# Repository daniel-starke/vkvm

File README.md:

vkvm
====

**V**irtual **K**eyboard **V**ideo **M**ouse equipment.  
This project consists of a software part which runs on the host (controller) computer and a hardware
unit (periphery). The periphery is connected via HDMI and USB to the USB port at the controller. The
controller uses this connection to control the connected periphery computer. Control works similar to
the control of a system running within a virtual machine.  
The vkvm ensures a non-intrusive connection to the periphery device. Therefore, no special drivers or
software is needed at the periphery. This grants maximum compatibility and high security not found in
VPN or SSH like solutions and works also before OS start-up (e.g. remote BIOS control).

```txt
+------------+       +----------------------+      +---------------+
|            |  <--- | Video Capture Device | <--- |               |
| Controller |       +----------------------+      | Remote Device |
|            |  <--> | VKVM Periphery       | <--> |               |
+------------+       +----------------------+      +---------------+
```

Features
========

- control application support for Windows and Linux
- USB UVC capture device compatible at controller
- USB HID boot keyboard/mouse compatible at periphery
- easy setup and use via plug'n'play
- cheap, small, low latency and portable design
- supports direct video output capture of periphery or web cam based operation
- multiple hardware variants are available to meet different hardware assembly skills and usage requirements
- remote device access before OS startup (e.g. enter BitLocker password or set BIOS settings)

Usage
=====

Use an available display to USB (not the other way around) converter to capture the video output
of a periphery machine at the controller. See chapter example for some possible variants. Connect
the VKVM hardware device to controller and periphery to control the keyboard and mouse of the
periphery via the controller. The vkvm control application enables you to perform the described hardware
connection on software level.  
Here you choose the connected capture source and serial interface which connects the vkvm hardware.
Click into the video frame to start controlling the remote device. Hit the right SHIFT and right CTRL key
to return control. Alternatively, press CTRL-K without a connected capture source for blind control.
This can be useful when controlling the periphery device with a connected physical monitor.  
To improve periphery operation, multiple ways of inputting data from controller (paste text) are provided.
Each type exists due to different compatibilities, either by applications or on OS level.  
Most of the user interface is made up of icons to avoid language barriers.

Status LED of the VKVM periphery:

|LED                  |State     |Meaning
|:-------------------:|----------|------------------------------------------------
|                     |always off|No remote device connected.
||blinking  |Power from remote device but not USB connection.
||always on |Fully connected to remote device.

Documentation
=============

- [Windows: VKVM Control Driver Installation](doc/win-driver.md)
- [Hardware](doc/hardware.md)
- [Software Architecture](doc/architecture.md)
- [Serial Protocol](doc/protocol.md)

Building
========

The following dependencies are given.  
Controller:  
- C99
- C++11
- [FLTK 1.3.4-1](https://github.com/fltk/fltk/tree/release-1.3.4-1)
- [nanosvg](https://github.com/memononen/nanosvg) (modified source included)
- OpenGL
- DirectShow (only on Windows)
- libv4l2 (only on Linux)
- lv4lconvert (only on Linux)

Periphery:  
- C18
- C++14
- [PlatformIO](https://platformio.org/)
- [STM32CubeDuino](https://github.com/daniel-starke/STM32CubeDuino)
- [HidDescCTC](https://github.com/daniel-starke/HidDescCTC)

Choose the appropriate Makefile to match your target system configuration.  
Windows with MinGW and GCC:  
```sh
make -f Makefile.mingw
```

Linux with GCC:
```sh
make -f Makefile.linux
```

This creates two applications:
- `vkvm`  
  The actual VKVM control application.
- `keyTest`  
  Development tool to create the OS key code to USB key code mapping.

To build and upload the firmware (depending on the target hardware):
```sh
pio run -e arduino -t upload
pio run -e vkm-b-controller -t upload
pio run -e vkm-b-periphery -t upload
```

Note that `VKVM_LED_PWM` for `vkm-b-periphery` can be changed in `platformio.ini` to any value
between 0 and 65535 to adjust the brightness of the status LED.

Also note that it is possible to set `upload_protocol = dfu` for `STM32CubeDuino` in `platformio.ini`
allowing first time programming via USB.

Open Points
===========

- [ ] command-line operations for instant video/serial connect and full screen switch
- [ ] automatically reconnect last serial/video device if it re-appears and was not disconnected by user
- [ ] alternative serial/video implementation using libusb/libuvc
- [ ] force aspect ratio option in aspect ratio button
- [ ] audio support
- [ ] configurable hot keys
- [ ] media key support (needs changes in the periphery firmware)
- [ ] fast store and load option for capture source settings
- [ ] option for file exchange via USB MTP (media transfer protocol)
- [ ] option for shared network access via USB ECM (Ethernet control model)

Limitation
==========

- keyboard and mouse input may not work with the Arduino firmware variant due to legacy BIOS
  incompatibilities with the CDC interface included by Arduino
- no OCR support (out of scope and can be done with existing screen reader applications)
- root permissions are required for the vkvm application on Linux

Debugging
=========

Choose the appropriate Makefile to match your target system configuration.  
Windows with MinGW and GCC:  
```sh
make -f Makefile.mingw DEBUG=1
```

Linux with GCC:
```sh
make -f Makefile.linux DEBUG=1
```

The macro `VKVM_TRACE` can be defined to create the serial trace file `vkvm.log`
during runtime. The GAWK script `script/prot-dec.awk` is able to decode this file into
a human readable format. The macro can be enabled by passing `TRACE=1` to Gnumake.

To debug the periphery firmware run:
```sh
pio debug -e vkm-b-periphery
pio run -e vkm-b-periphery -t upload -t nobuild
pio debug  -e vkm-b-periphery --interface=gdb -- -x .pioinit
```

The HID reports on the periphery device can be traced using
Wireshark (see [description](https://wiki.wireshark.org/CaptureSetup/USB)).

In Linux it is also possible to read and analyze the HID reports
with the following command:
```sh
cat /sys/kernel/debug/<dev>/events
```

This shows how the Linux HID driver interprets the HID reports.

License
=======

See [LICENSE](LICENSE).  

Contributions
=============

No content contributions are accepted. Please file a bug report or feature request instead.  
This decision was made in consideration of the used license.

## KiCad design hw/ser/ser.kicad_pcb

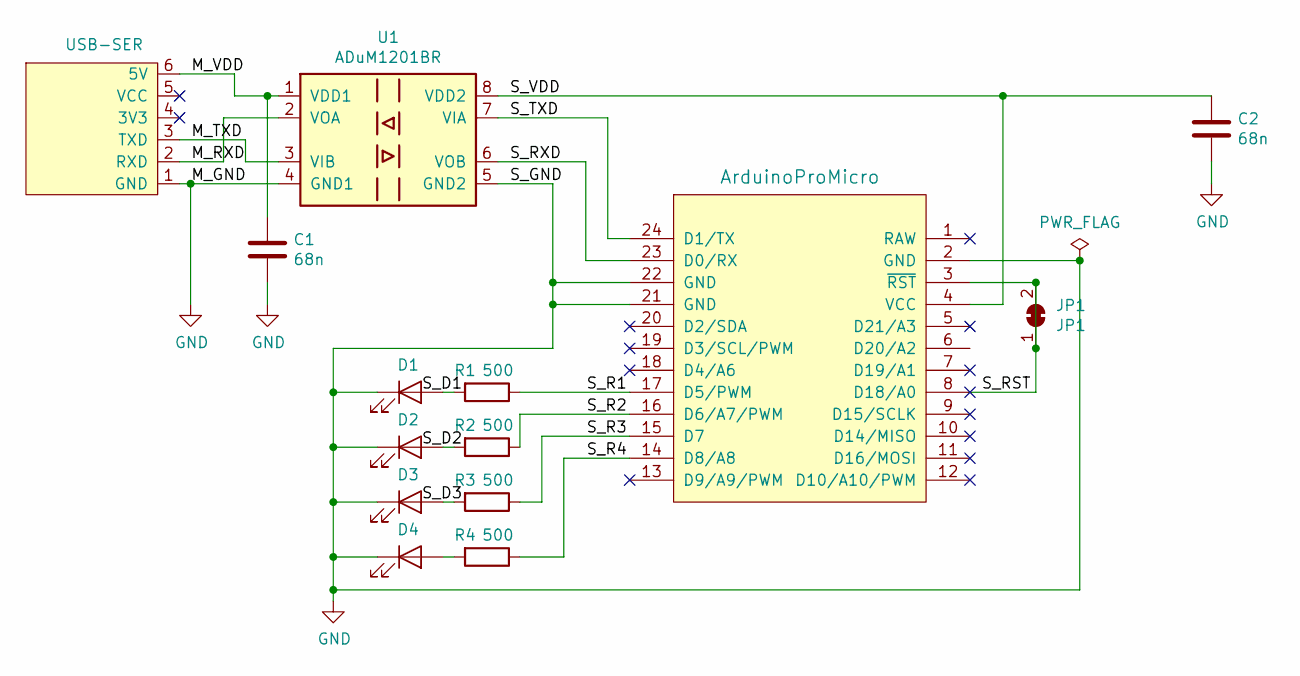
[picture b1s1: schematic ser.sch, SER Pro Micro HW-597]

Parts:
C1, C2: 68n; C_0603_1608Metric_Pad1.05x0.95mm_HandSolder
D1, D2, D3, D4: LED; LED_0603_1608Metric_Pad1.05x0.95mm_HandSolder
IC1: ArduinoProMicro; ArduinoProMicro_Custom
JP1: JP1; SolderJumper-2_P1.3mm_Bridged_Pad1.0x1.5mm
JT1: USB-SER; PinHeader_1x06_P2.54mm_Vertical_Custom
R1, R2, R3, R4: 500; R_0603_1608Metric_Pad1.05x0.95mm_HandSolder
U1: ADuM1201BR; SOIC-8_3.9x4.9mm_P1.27mm

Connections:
/M_RXD: JT1.2 (RXD), U1.2 (VOA)
/M_TXD: JT1.3 (TXD), U1.3 (VIB)
/M_VDD: C1.1, JT1.6 (5V), U1.1 (VDD1)
/S_R1: IC1.17 (D5/PWM), R1.1
/S_R2: IC1.16 (D6/A7/PWM), R2.1
/S_R3: IC1.15 (D7), R3.1
/S_R4: IC1.14 (D8/A8), R4.1
/S_RST: IC1.3 (~RST), IC1.8 (D18/A0), JP1.1 (A), JP1.2 (B)
/S_RXD: IC1.23 (D0/RX), U1.6 (VOB)
/S_TXD: IC1.24 (D1/TX), U1.7 (VIA)
/S_VDD: C2.1, IC1.4 (VCC), U1.8 (VDD2)
GND: C1.2, C2.2, D1.1 (K), D2.1 (K), D3.1 (K), D4.1 (K), IC1.2 (GND), IC1.21 (GND), IC1.22 (GND), JT1.1 (GND), U1.4 (GND1), U1.5 (GND2)
unnamed: D1.2 (A), R1.2
unnamed: D2.2 (A), R2.2
unnamed: D3.2 (A), R3.2
unnamed: D4.2 (A), R4.2

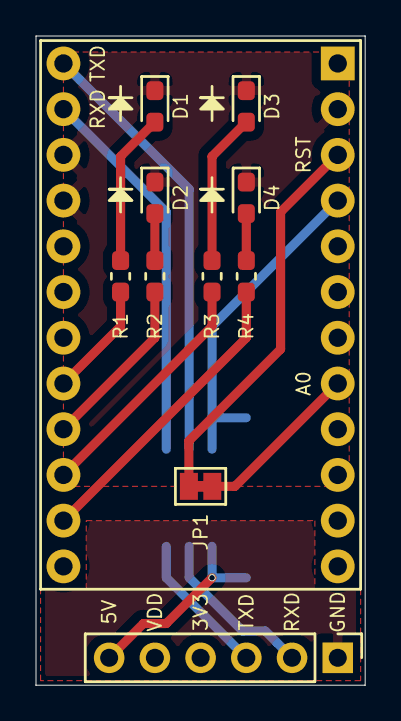
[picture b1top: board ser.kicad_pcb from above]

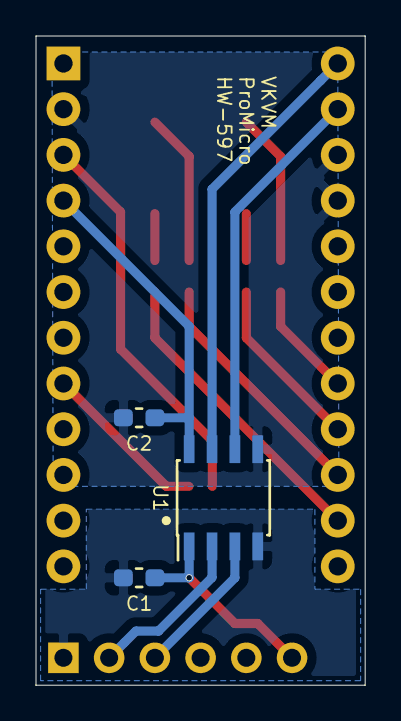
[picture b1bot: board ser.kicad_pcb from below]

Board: 2 copper layers, 18.3 x 36.1 mm, 14 parts (3 on the bottom side), 16 nets.

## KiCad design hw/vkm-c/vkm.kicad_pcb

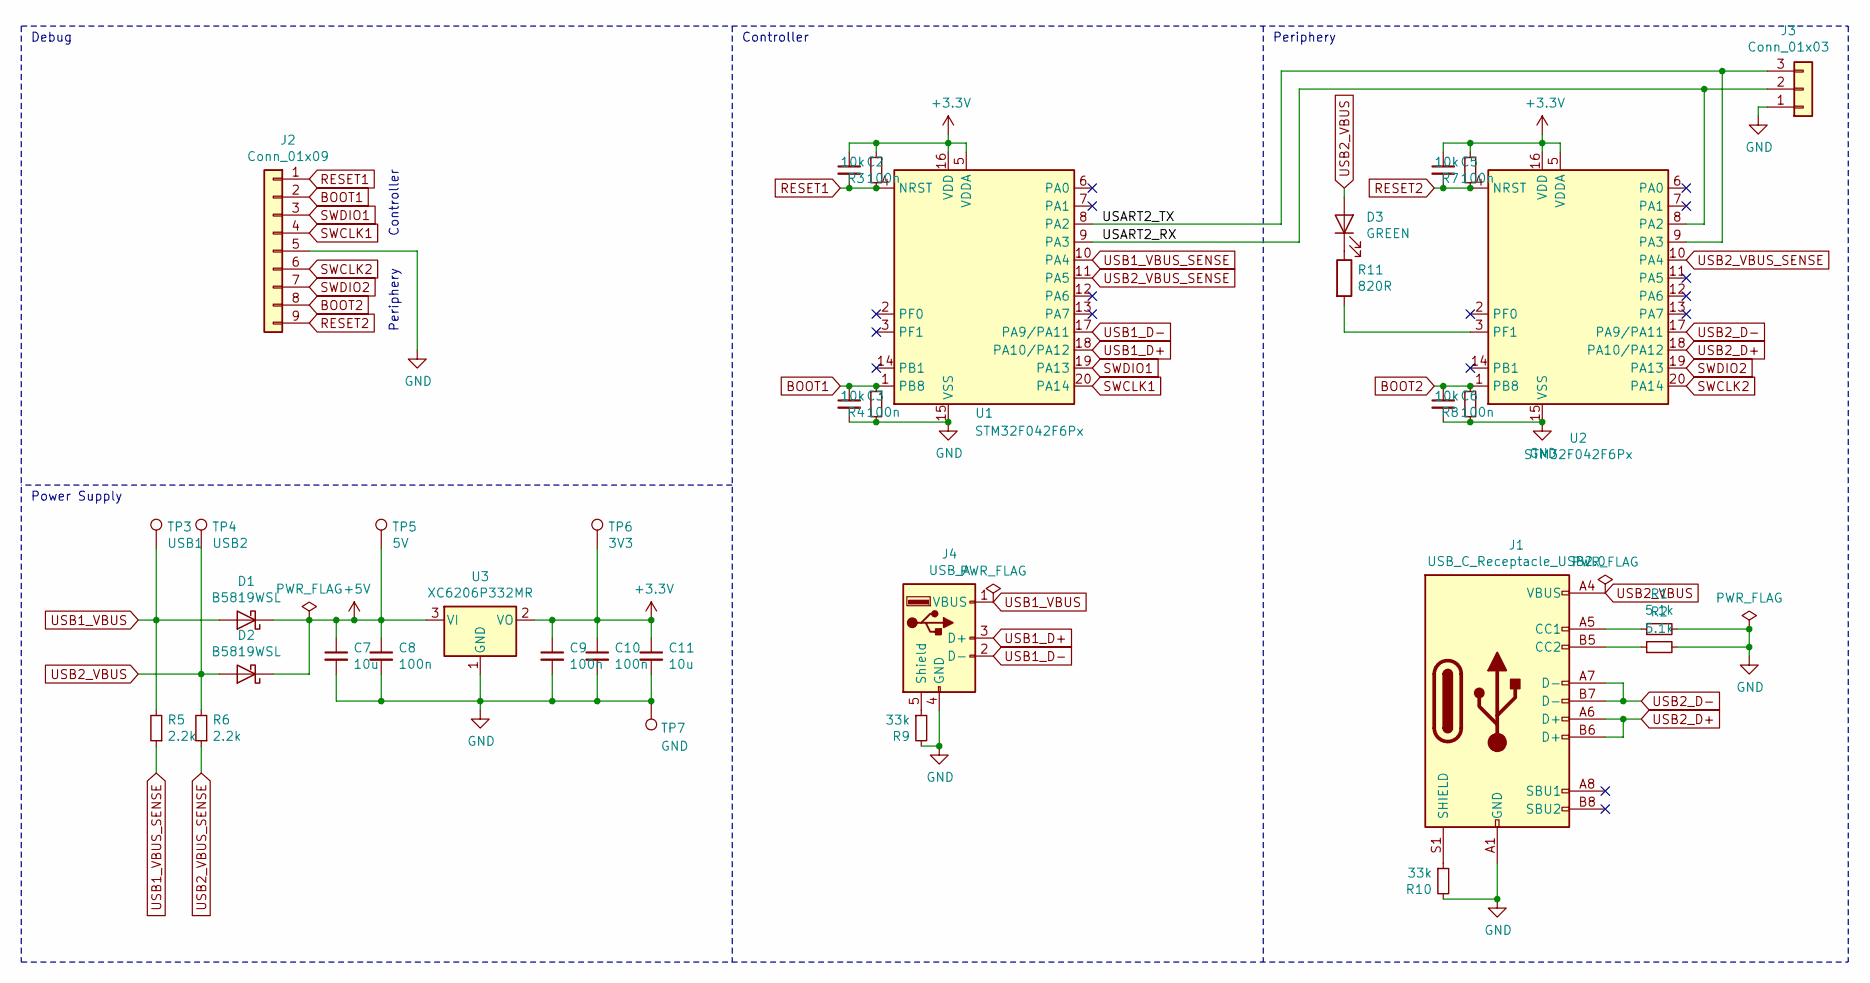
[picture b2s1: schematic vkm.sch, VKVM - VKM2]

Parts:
C2, C3, C5, C6, C8, C9, C10: 100n; C_0603_1608Metric; LCSC C14663
C7, C11: 10u; C_0603_1608Metric; LCSC C19702
D1, D2: B5819WSL; D_SOD-123; LCSC C8598
D3: GREEN; LED_0603_1608Metric; LCSC C72043
J1: USB_C_Receptacle_USB2.0; USB_C_HRO_TYPE_C_31_M_12; LCSC C165948
J2: Conn_01x09; PinHeader_1x09_P2.54mm_Vertical
J3: Conn_01x03; PinHeader_1x03_P2.54mm_Horizontal_Edge
J4: USB_A; USB_A_TH_AM90; LCSC C9739
R1, R2: 5.1k; R_0603_1608Metric; LCSC C23186
R3, R4, R7, R8: 10k; R_0603_1608Metric; LCSC C25804
R5, R6: 2.2k; R_0603_1608Metric; LCSC C4190
R9, R10: 33k; R_0603_1608Metric; LCSC C4216
R11: 820R; R_0603_1608Metric; LCSC C23253
TP3: USB1; TestPoint_Pad_D1.0mm
TP4: USB2; TestPoint_Pad_D1.0mm
TP5: 5V; TestPoint_Pad_D1.0mm
TP6: 3V3; TestPoint_Pad_D1.0mm
TP7: GND; TestPoint_Pad_D1.0mm
U1, U2: STM32F042F6Px; TSSOP-20_4.4x6.5mm_P0.65mm; LCSC C81000
U3: XC6206P332MR; SOT-23; LCSC C5446

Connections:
+3V3: C2.1, C5.1, C9.1, C10.1, C11.1, R3.1, R7.1, TP6.1, U1.5 (VDDA), U1.16 (VDD), U2.5 (VDDA), U2.16 (VDD), U3.2 (VO)
+5V: C7.1, C8.1, D1.1 (K), D2.1 (K), TP5.1, U3.3 (VI)
/USART2_RX: J3.2, U1.9 (PA3), U2.8 (PA2)
/USART2_TX: J3.3, U1.8 (PA2), U2.9 (PA3)
BOOT1: C3.1, J2.2, R4.1, U1.1 (PB8)
BOOT2: C6.1, J2.8, R8.1, U2.1 (PB8)
GND: C3.2, C6.2, C7.2, C8.2, C9.2, C10.2, C11.2, J1.A1 (GND), J1.A12 (GND), J1.B1 (GND), J1.B12 (GND), J2.5, J3.1, J4.4 (GND), R1.2, R2.2, R4.2, R8.2, R9.2, R10.2, TP7.1, U1.15 (VSS), U2.15 (VSS), U3.1 (GND)
unnamed: D3.1 (K), R11.1
unnamed: J1.A5 (CC1), R1.1
unnamed: J1.B5 (CC2), R2.1
unnamed: J1.S1 (SHIELD), R10.1
unnamed: J4.5 (Shield), R9.1
unnamed: R11.2, U2.3 (PF1)
RESET1: C2.2, J2.1, R3.2, U1.4 (NRST)
RESET2: C5.2, J2.9, R7.2, U2.4 (NRST)
SWCLK1: J2.4, U1.20 (PA14)
SWCLK2: J2.6, U2.20 (PA14)
SWDIO1: J2.3, U1.19 (PA13)
SWDIO2: J2.7, U2.19 (PA13)
USB1_D+: J4.3 (D+), U1.18 (PA10/PA12)
USB1_D-: J4.2 (D-), U1.17 (PA9/PA11)
USB1_VBUS: D1.2 (A), J4.1 (VBUS), R5.2, TP3.1
USB1_VBUS_SENSE: R5.1, U1.10 (PA4)
USB2_D+: J1.A6 (D+), J1.B6 (D+), U2.18 (PA10/PA12)
USB2_D-: J1.A7 (D-), J1.B7 (D-), U2.17 (PA9/PA11)
USB2_VBUS: D2.2 (A), D3.2 (A), J1.A4 (VBUS), J1.A9 (VBUS), J1.B4 (VBUS), J1.B9 (VBUS), R6.2, TP4.1
USB2_VBUS_SENSE: R6.1, U1.11 (PA5), U2.10 (PA4)

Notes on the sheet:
Controller
Periphery
Debug
Power Supply

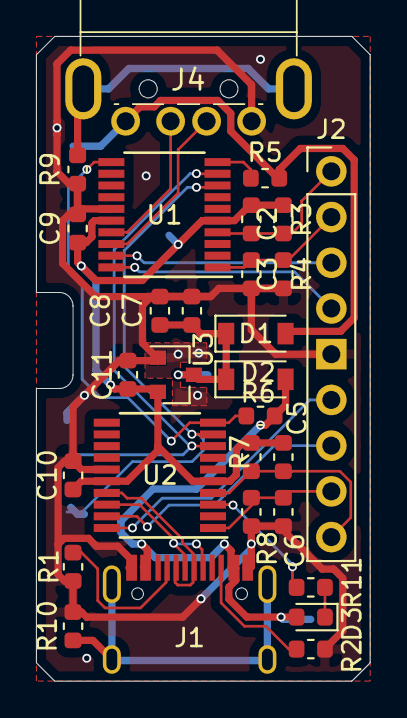
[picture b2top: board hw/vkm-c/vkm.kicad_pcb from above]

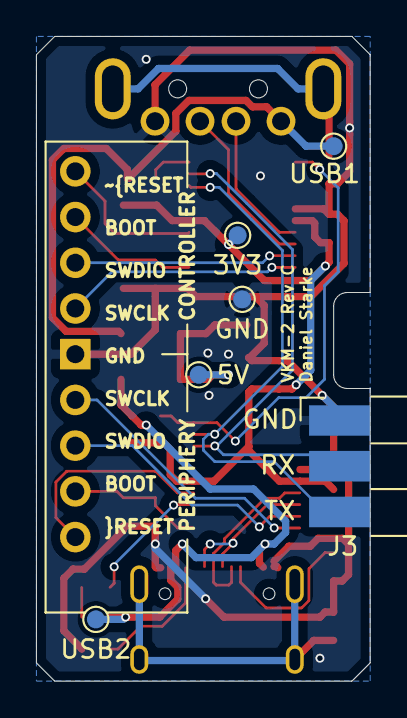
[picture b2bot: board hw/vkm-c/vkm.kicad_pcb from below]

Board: 2 copper layers, 18.5 x 35.8 mm, 35 parts (6 on the bottom side), 27 nets.

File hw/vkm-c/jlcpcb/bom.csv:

Comment,Designator,Footprint,LCSC
10u,"C7,C11",Capacitor_SMD:C_0603_1608Metric,C19702
100n,"C8,C9,C10,C2,C3,C6,C5",Capacitor_SMD:C_0603_1608Metric,C14663
B5819WSL,"D1,D2",Diode_SMD:D_SOD-123,C8598
GREEN,D3,LED_SMD:LED_0603_1608Metric,C72043
USB_C_Receptacle_USB2.0,J1,Connector_USB:USB_C_HRO_TYPE_C_31_M_12,C165948
Conn_01x09,J2,Connector_PinHeader_2.54mm:PinHeader_1x09_P2.54mm_Vertical,
Conn_01x03,J3,vkm-c:PinHeader_1x03_P2.54mm_Horizontal_Edge,
USB_A,J4,Connector_USB:USB_A_TH_AM90,C9739
5.1k,"R1,R2",Resistor_SMD:R_0603_1608Metric,C23186
33k,"R10,R9",Resistor_SMD:R_0603_1608Metric,C4216
820R,R11,Resistor_SMD:R_0603_1608Metric,C23253
10k,"R3,R7,R4,R8",Resistor_SMD:R_0603_1608Metric,C25804
2.2k,"R6,R5",Resistor_SMD:R_0603_1608Metric,C4190
USB1,TP3,TestPoint:TestPoint_Pad_D1.0mm,
USB2,TP4,TestPoint:TestPoint_Pad_D1.0mm,
5V,TP5,TestPoint:TestPoint_Pad_D1.0mm,
3V3,TP6,TestPoint:TestPoint_Pad_D1.0mm,
GND,TP7,TestPoint:TestPoint_Pad_D1.0mm,
STM32F042F6Px,"U1,U2",Package_SO:TSSOP-20_4.4x6.5mm_P0.65mm,C81000
XC6206P332MR,U3,Package_TO_SOT_SMD:SOT-23,C5446

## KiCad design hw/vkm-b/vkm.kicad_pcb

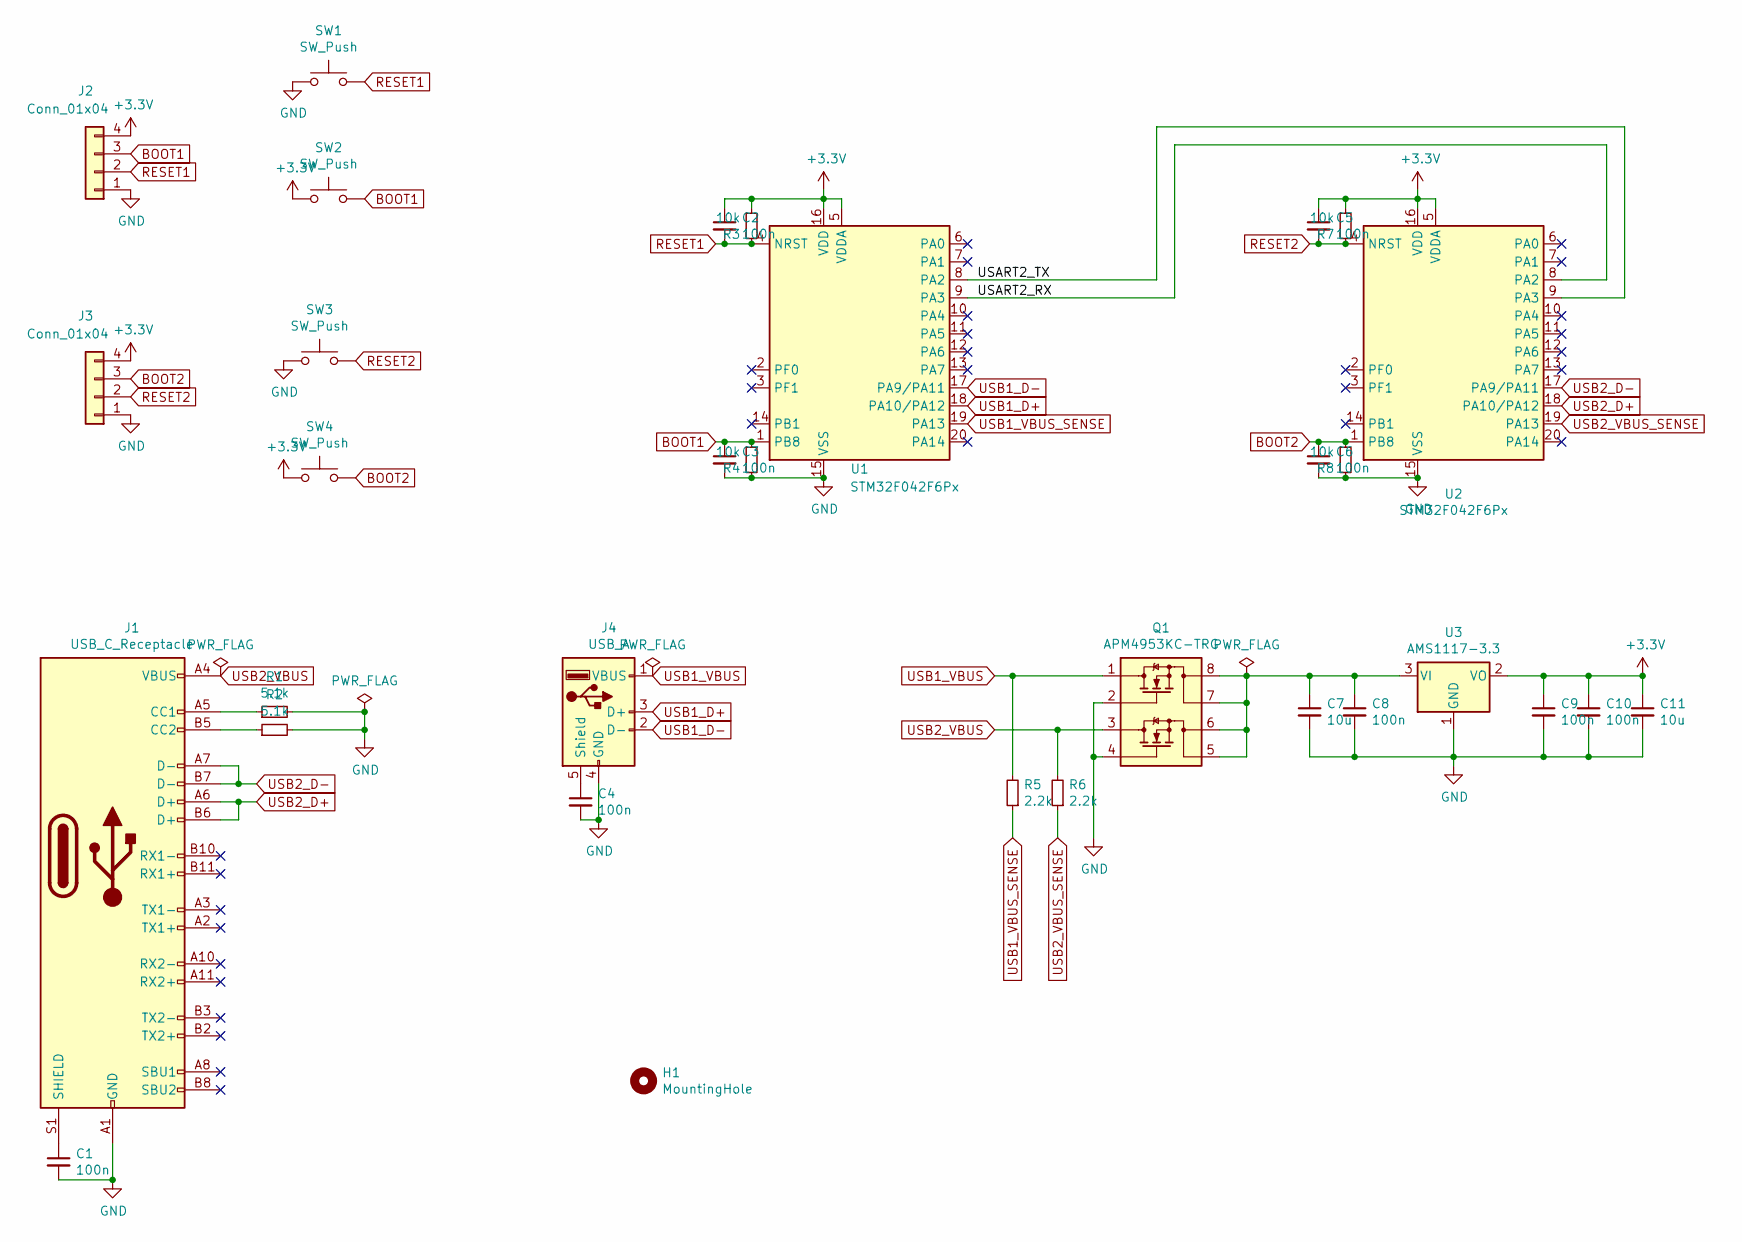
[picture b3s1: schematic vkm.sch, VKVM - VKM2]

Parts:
C1, C2, C3, C4, C5, C6, C8, C9, C10: 100n; C_0603_1608Metric; LCSC C14663
C7, C11: 10u; CP_EIA-3216-10_Kemet-I; LCSC C7171
H1: MountingHole; MountingHole_3.2mm_M3_DIN965_Pad
J1: USB_C_Receptacle; USB_C_HRO_TYPE_C_31_M_12; LCSC C165948
J2, J3: Conn_01x04; PinHeader_1x04_P2.54mm_Vertical
J4: USB_A; USB_A_TH_AM90; LCSC C9739
Q1: APM4953KC-TRG; SOP-8_3.9x4.9mm_P1.27mm; LCSC C20897
R1, R2: 5.1k; R_0603_1608Metric; LCSC C23186
R3, R4, R7, R8: 10k; R_0603_1608Metric; LCSC C25804
R5, R6: 2.2k; R_0603_1608Metric; LCSC C4190
SW1, SW2, SW3, SW4: SW_Push; SW_SPST_TL3342
U1, U2: STM32F042F6Px; TSSOP-20_4.4x6.5mm_P0.65mm; LCSC C81000
U3: AMS1117-3.3; SOT-223-3_TabPin2; LCSC C6186

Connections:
+3V3: C2.1, C5.1, C9.1, C10.1, C11.1, J2.4, J3.4, R3.1, R7.1, SW2.1, SW4.1, U1.5 (VDDA), U1.16 (VDD), U2.5 (VDDA), U2.16 (VDD), U3.2 (VO)
/USART2_RX: U1.9 (PA3), U2.8 (PA2)
/USART2_TX: U1.8 (PA2), U2.9 (PA3)
BOOT1: C3.1, J2.3, R4.1, SW2.2, U1.1 (PB8)
BOOT2: C6.1, J3.3, R8.1, SW4.2, U2.1 (PB8)
GND: C1.2, C3.2, C4.2, C6.2, C7.2, C8.2, C9.2, C10.2, C11.2, J1.A1 (GND), J1.A12 (GND), J1.B1 (GND), J1.B12 (GND), J2.1, J3.1, J4.4 (GND), Q1.2 (G1), Q1.4 (G2), R1.2, R2.2, R4.2, R8.2, SW1.1, SW3.1, U1.15 (VSS), U2.15 (VSS), U3.1 (GND)
unnamed: C1.1, J1.S1 (SHIELD)
unnamed: C4.1, J4.5 (Shield)
unnamed: C7.1, C8.1, Q1.5 (D2), Q1.6 (D2), Q1.7 (D1), Q1.8 (D1), U3.3 (VI)
unnamed: J1.A5 (CC1), R1.1
unnamed: J1.B5 (CC2), R2.1
RESET1: C2.2, J2.2, R3.2, SW1.2, U1.4 (NRST)
RESET2: C5.2, J3.2, R7.2, SW3.2, U2.4 (NRST)
USB1_D+: J4.3 (D+), U1.18 (PA10/PA12)
USB1_D-: J4.2 (D-), U1.17 (PA9/PA11)
USB1_VBUS: J4.1 (VBUS), Q1.1 (S1), R5.2
USB1_VBUS_SENSE: R5.1, U1.19 (PA13)
USB2_D+: J1.A6 (D+), J1.B6 (D+), U2.18 (PA10/PA12)
USB2_D-: J1.A7 (D-), J1.B7 (D-), U2.17 (PA9/PA11)
USB2_VBUS: J1.A4 (VBUS), J1.A9 (VBUS), J1.B4 (VBUS), J1.B9 (VBUS), Q1.3 (S2), R6.2
USB2_VBUS_SENSE: R6.1, U2.19 (PA13)

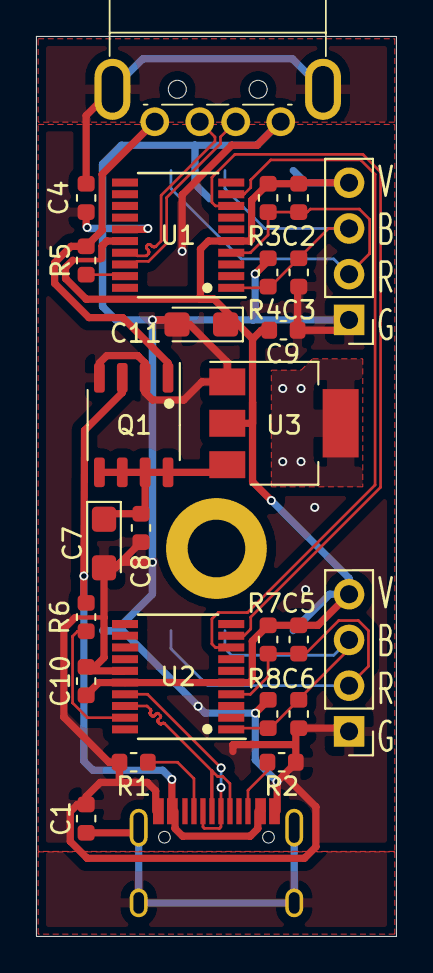
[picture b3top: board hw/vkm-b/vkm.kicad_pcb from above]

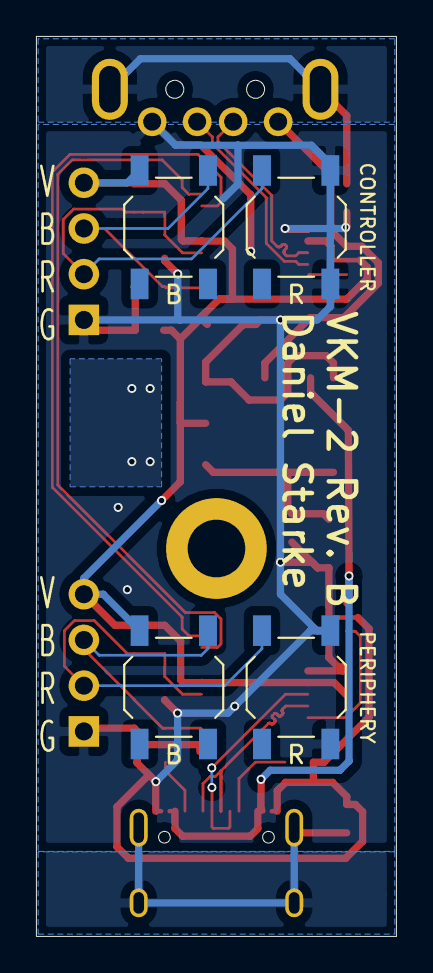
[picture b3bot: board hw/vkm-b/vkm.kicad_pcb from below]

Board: 2 copper layers, 20.0 x 50.0 mm, 32 parts (4 on the bottom side), 21 nets.

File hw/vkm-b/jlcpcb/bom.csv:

Comment,Designator,Footprint,LCSC
"10u","C7,C11","Capacitor_Tantalum_SMD:CP_EIA-3216-10_Kemet-I","C7171"
"100n","C8,C9,C10,C4,C1,C2,C3,C6,C5","Capacitor_SMD:C_0603_1608Metric","C14663"
"APM4953KC-TRG","Q1","Package_SO:SOP-8_3.9x4.9mm_P1.27mm","C20897"
"5.1k","R1,R2","Resistor_SMD:R_0603_1608Metric","C23186"
"10k","R3,R7,R4,R8","Resistor_SMD:R_0603_1608Metric","C25804"
"2.2k","R6,R5","Resistor_SMD:R_0603_1608Metric","C4190"
"STM32F042F6Px","U1,U2","Package_SO:TSSOP-20_4.4x6.5mm_P0.65mm","C81000"
"AMS1117-3.3","U3","Package_TO_SOT_SMD:SOT-223-3_TabPin2","C6186"

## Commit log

2023-11-08 Initial commit.
2023-11-08 Apply various small fixes.
    - added: build badges in README.md
    - fixed: syntax error in appveyor.yml
    - fixed: wrong cast type in CaptureVideo4Linux2.ipp
2023-11-08 Fix CI scripts.
2023-11-08 Fix further issues in the CI scripts.
2023-11-08 Fix AppVeyor multiline command issue.
2023-11-08 Fix AppVeyor artifact path to be relative.
2023-11-15 Add Windows Controller device driver installation guide.
2023-11-15 Fix new line formatting in win-driver.md.
2023-11-19 Add HDMI capture variant 5. Fix description of 3 and 4.
    - added: HDMI capture variant 5
    - fixed: description of HDMI capture variant 3 and 4
2023-12-08 1.1.0
    - add: description for HDMI Capture Variant 6
    - add: ComPtr implementation for Windows targets
    - change: add video device index number in capture device list on Linux
    - change: use ComPtr based object life-time management in DirectShow related code
    - fix: missing capture devices if multiple share the same name
    - fix: ignore non-capture capable video devices on Linux
2023-12-09 Change window size on capture start.
    Change the window size accourding to the capture size on capture start.
    Also fix misleading status output on capture stop.
2024-02-15 1.2.0
    - added: root privileges enforcement on Linux
2024-02-15 Add missing file for 1.2.0.
2024-02-19 1.2.1
    - fixed: broken mouse capture handling for none default DPI systems on Windows
    - fixed: broken meta key reset after input capturing on Windows
2024-02-23 1.2.2
    - fixed: missing explicit cleanup of password string for sudo on Linux
2024-11-04 1.2.3
    - added: description for HDMI Capture Variant 7
    - changed: internal sorting algorithm to a stable sorting variant
    - fixed: special characters handling in video and serial drop-down list
    - fixed: duplicate name case for video devices handling by adding the device path
    - fixed: missing linker plugin flag for LTO build
2024-11-04 Added missing reference to HDMI capture device variant 7.
2026-06-15 1.3.0
    - added: added periphery USB HID boot protocol mode indicator
    - changed: improved SVG rendering performance by caching blended images
    - changed: use double based absolute mouse positioning at Vkvm API
    - changed: use proper anti-aliased radio buttons in send keys popup menu
    - changed: use libv4lconvert to do the capture image conversion manually on Linux
    - fixed: incorrect internal result value for key releases within the firmware
2026-06-15 Fix CI depricated script actions.
2026-06-15 Fix missing includes.
2026-06-15 Fix AppVeyor build.
2026-06-15 Fix missing system libraries for MSys2/MinGW build.
2026-06-15 Fix wrong AppVeyor build toolchain.
2026-06-15 Fix wrong AppVeyor build toolchain prefix.
2026-06-15 Revert AppVeyor build.
